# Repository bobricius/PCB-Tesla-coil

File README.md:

# PCB-Tesla-coil
Simple Open PCB Tesla coil

Very easy Tesla Coil ... 3 components only = LED, BUL45DG2 transistor and 82K resistor

Hackday is my daily inspiration, every day found something interesting like this
http://www.megavolts.nl/en/projecten/tesla-spoelen/201-pcb-spiral-teslacoil
It is nice project but very complicated.

I have no idea how exactly tesla coil work, but I try glue all my knowledge and almost all is just experiments try and mistake ... 

But this project is much more easy and opensource,
effectivity is far away from original.
Everybody can improve it ...

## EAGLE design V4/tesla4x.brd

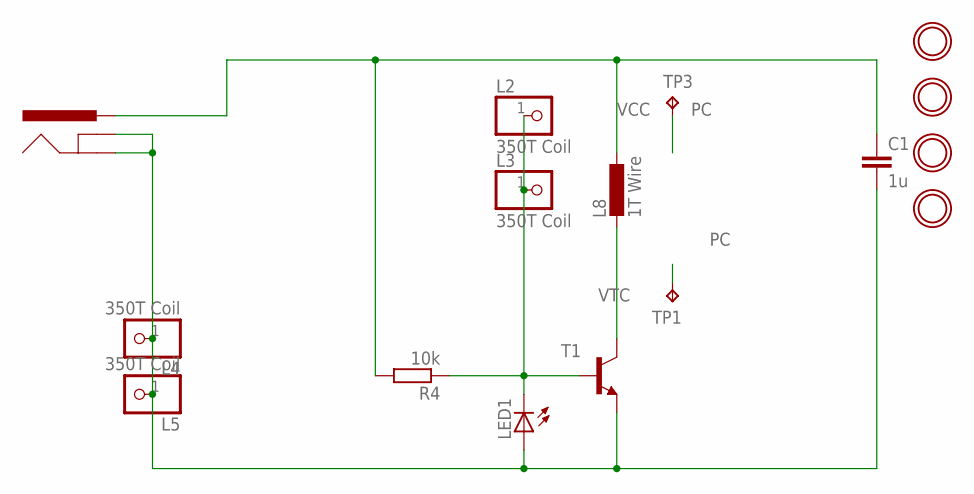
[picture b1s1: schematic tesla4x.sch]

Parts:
C1: 1u; C050-025X075
J1: POWER_JACKPTH; POWER_JACK_PTH
L2, L3, L4, L5: 350T Coil; 1X01
L8: 1T Wire; 0204/7
LED1: LED3MM
R4: 10k; 0207/7
T1: -NPN-TO220; TO220
TP1: TPTP20SQ; TP20SQ
TP3: TPTP20R; TP20R
U$1, U$2, U$3, U$4: MOUNTINGHOLE3.0THIN; MOUNTINGHOLE_3.0_PLATEDTHIN

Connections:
GND: C1.2, J1.GND, J1.GNDBREAK, L4.1, L5.1, LED1.A, T1.3 (E)
HV1: L2.1, L3.1, LED1.K (C), R4.1, T1.1 (B)
PC: TP1.TP, TP3.TP
VCC: C1.1, J1.PWR, L8.1, R4.2
VTC: L8.2, T1.2 (C)

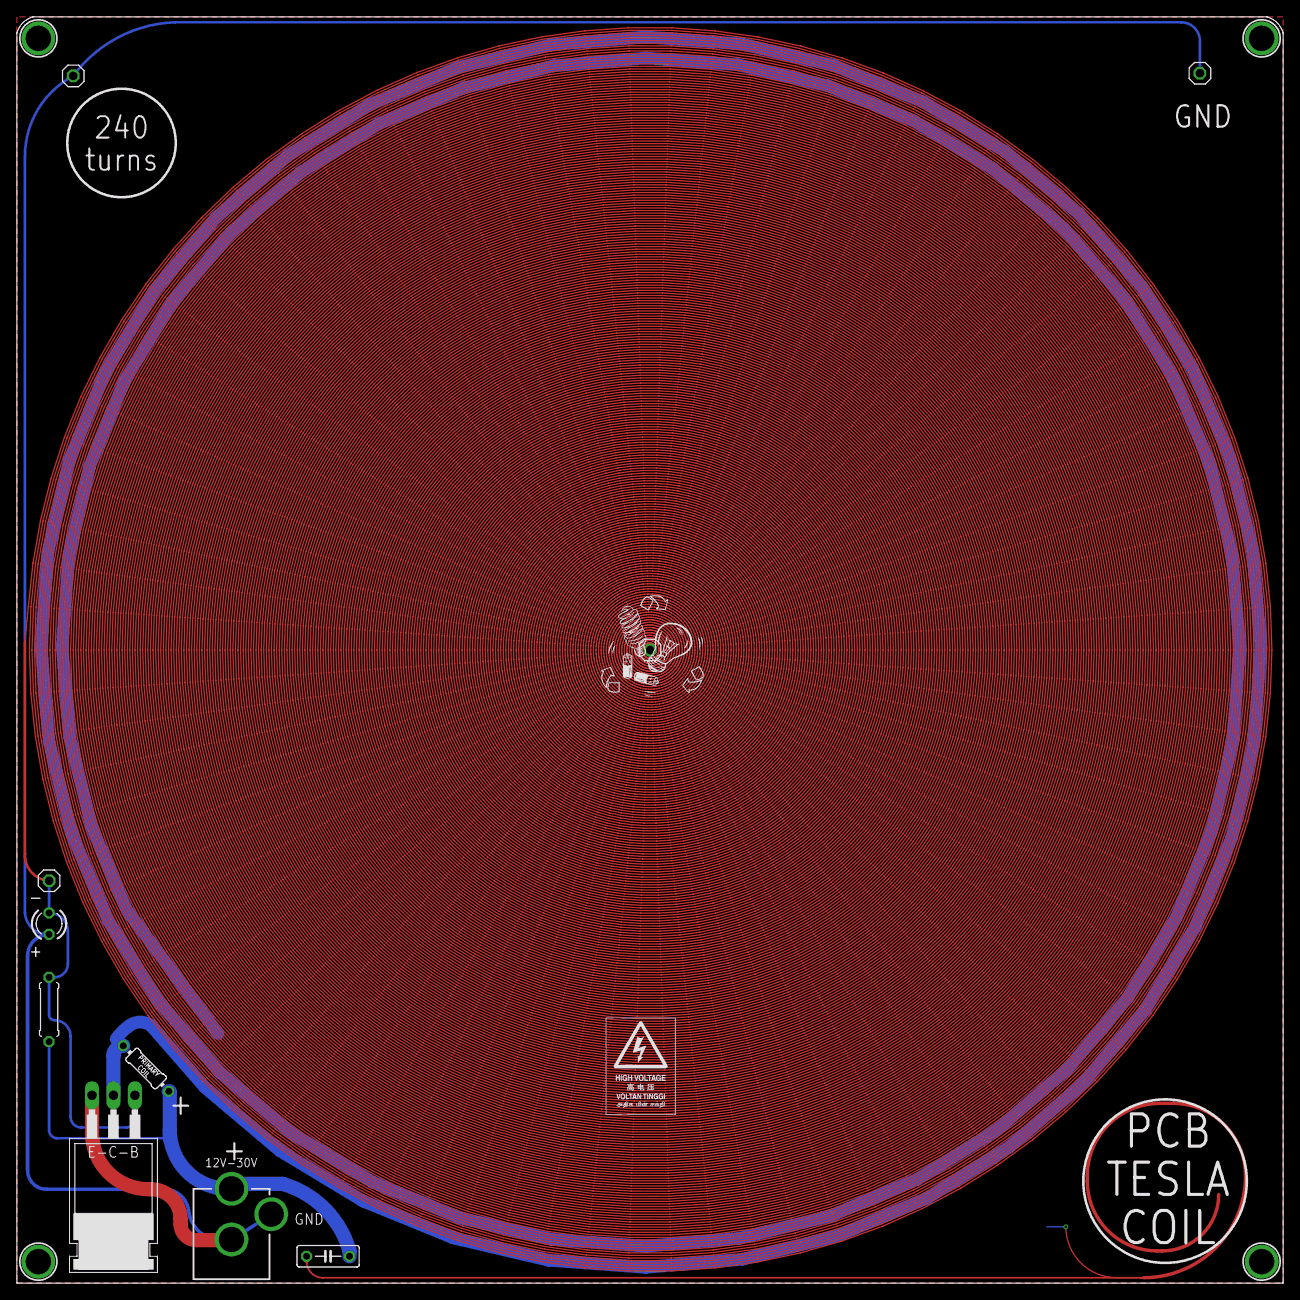
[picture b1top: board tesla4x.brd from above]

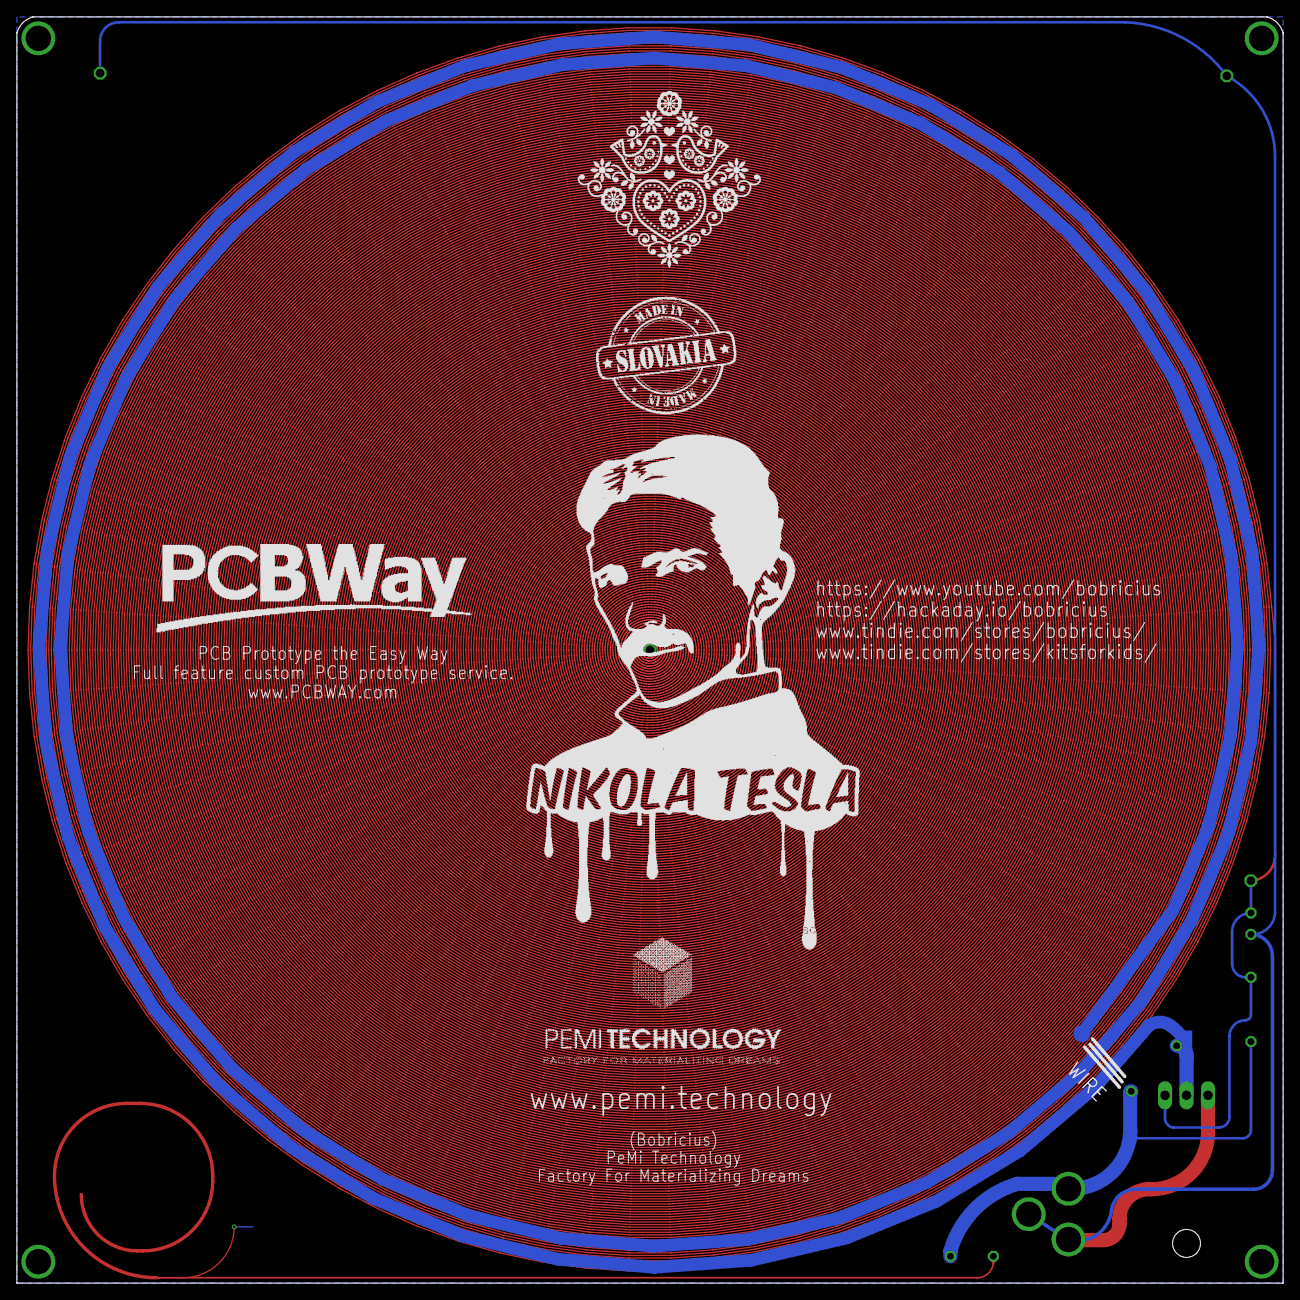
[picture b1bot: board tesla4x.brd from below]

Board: 2 copper layers, 149.9 x 149.9 mm, 17 parts (2 on the bottom side), 5 nets.

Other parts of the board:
U$5: HV03

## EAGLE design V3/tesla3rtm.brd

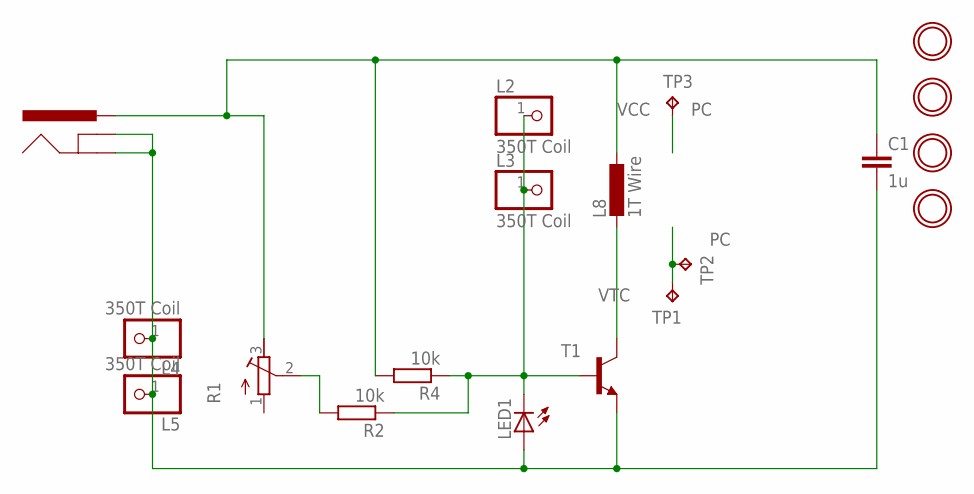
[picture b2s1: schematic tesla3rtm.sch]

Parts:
C1: 1u; C050-025X075
J1: POWER_JACKPTH; POWER_JACK_PTH
L2, L3, L4, L5: 350T Coil; 1X01
L8: 1T Wire; 0204/7
LED1: LED3MM
R1: R-TRIMM3339P; RTRIM3339P
R2, R4: 10k; 0207/7
T1: -NPN-TO220; TO220
TP1: TPTP20SQ; TP20SQ
TP2: TPTP16R; TP16R
TP3: TPTP20R; TP20R
U$1, U$2, U$3, U$4: MOUNTINGHOLE3.0THIN; MOUNTINGHOLE_3.0_PLATEDTHIN

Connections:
GND: C1.2, J1.GND, J1.GNDBREAK, L4.1, L5.1, LED1.A, T1.3 (E)
HV1: L2.1, L3.1, LED1.K (C), R2.1, R4.1, T1.1 (B)
unnamed: R1.2 (S), R2.2
PC: TP1.TP, TP2.TP, TP3.TP
VCC: C1.1, J1.PWR, L8.1, R1.3 (E), R4.2
VTC: L8.2, T1.2 (C)

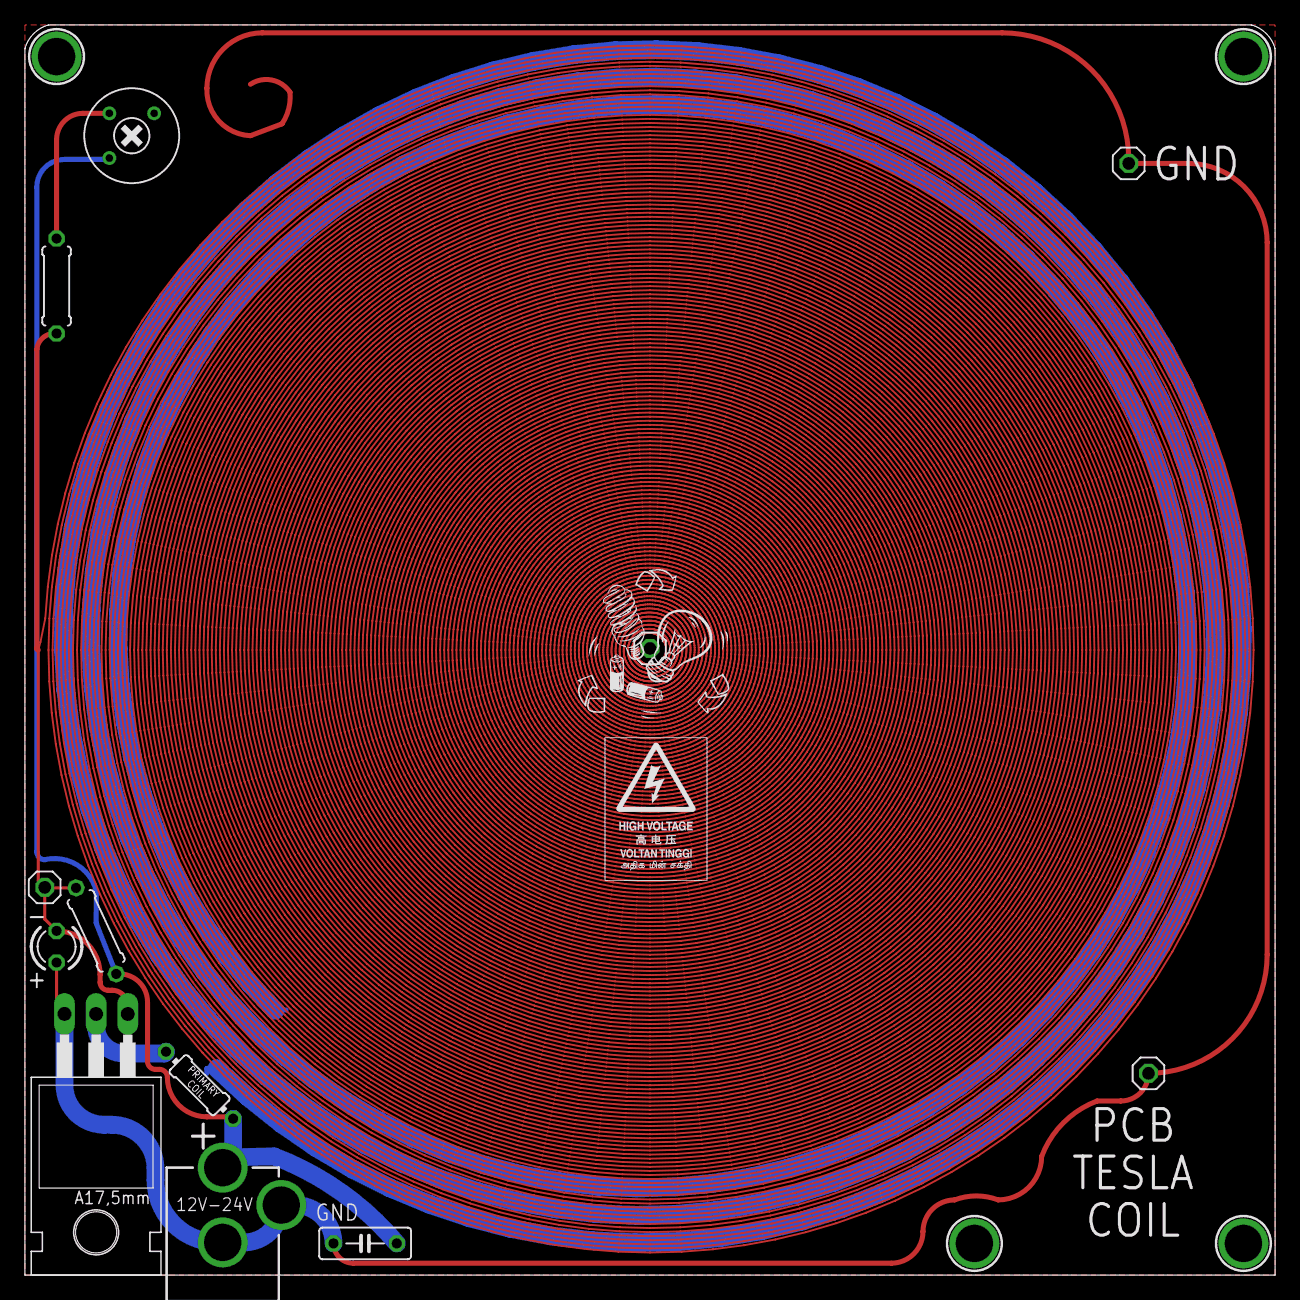
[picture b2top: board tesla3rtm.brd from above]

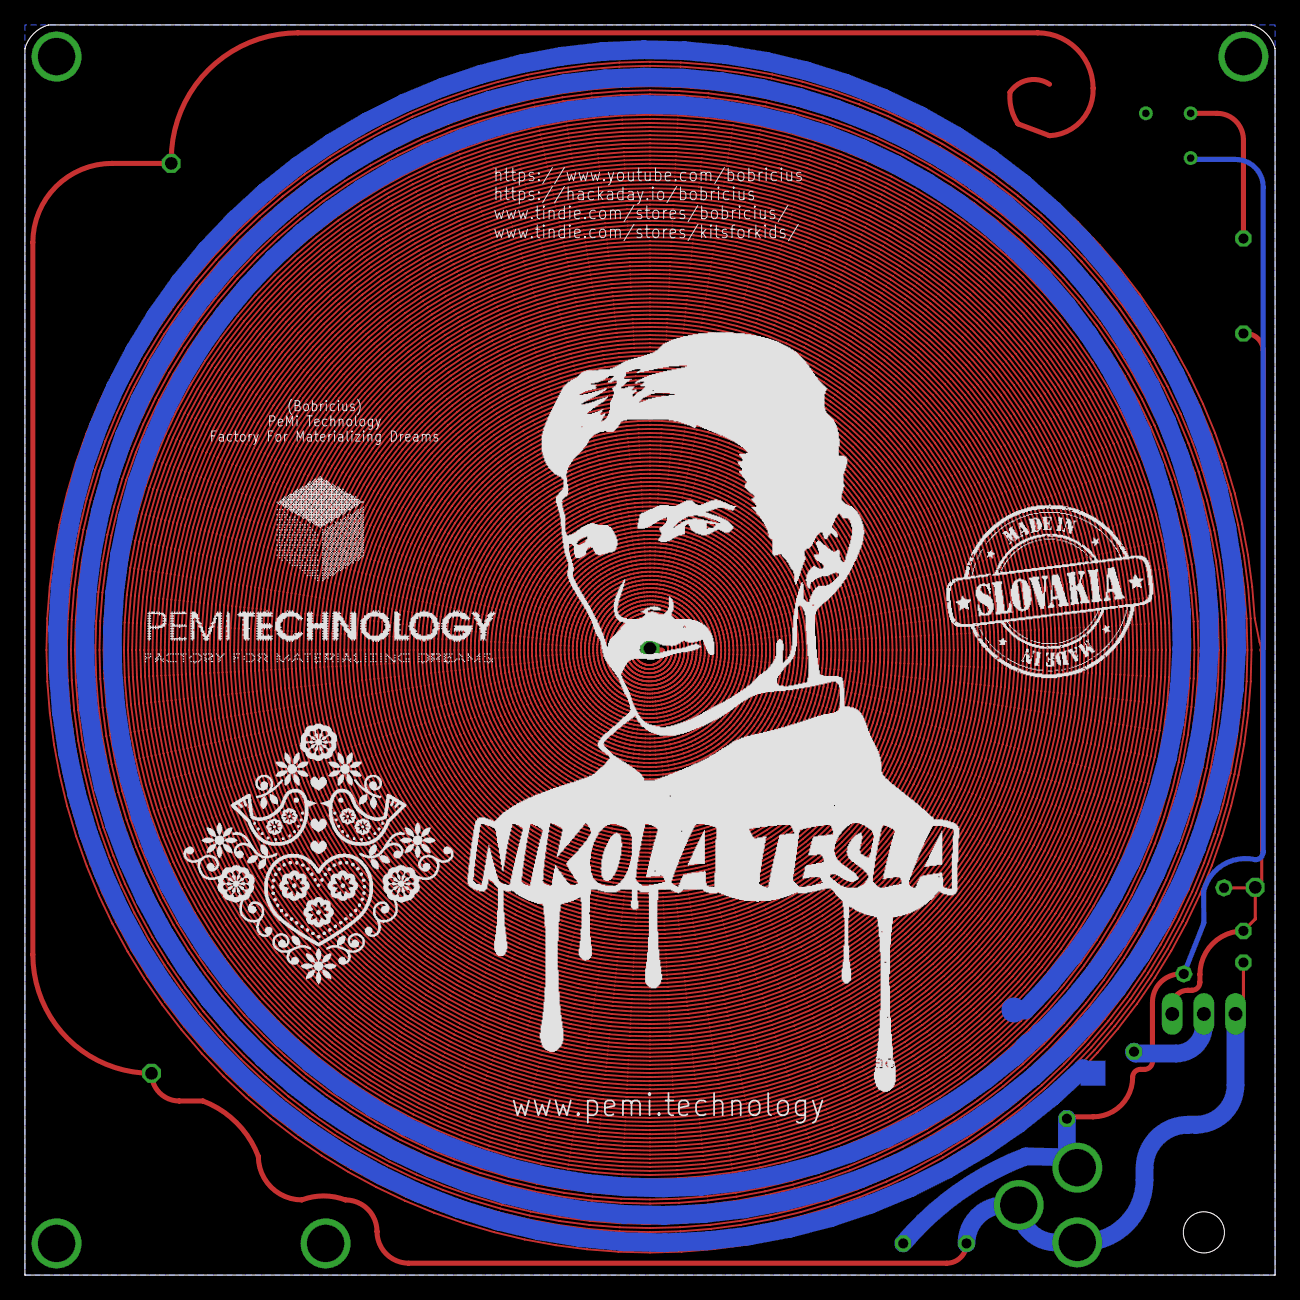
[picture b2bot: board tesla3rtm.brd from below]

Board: 2 copper layers, 100.3 x 100.3 mm, 20 parts (3 on the bottom side), 6 nets.

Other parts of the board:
U$5: HV03

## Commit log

2019-04-25 Add files via upload
    v3 and v4 design files

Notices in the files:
parts and their libraries:
microbuilder: This work is placed in the public domain, and may be freely used for commercial and non-commercial work with the following conditions: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
SparkFun: Licensing: CC v3.0 Share-Alike You are welcome to use this library for commercial purposes.
